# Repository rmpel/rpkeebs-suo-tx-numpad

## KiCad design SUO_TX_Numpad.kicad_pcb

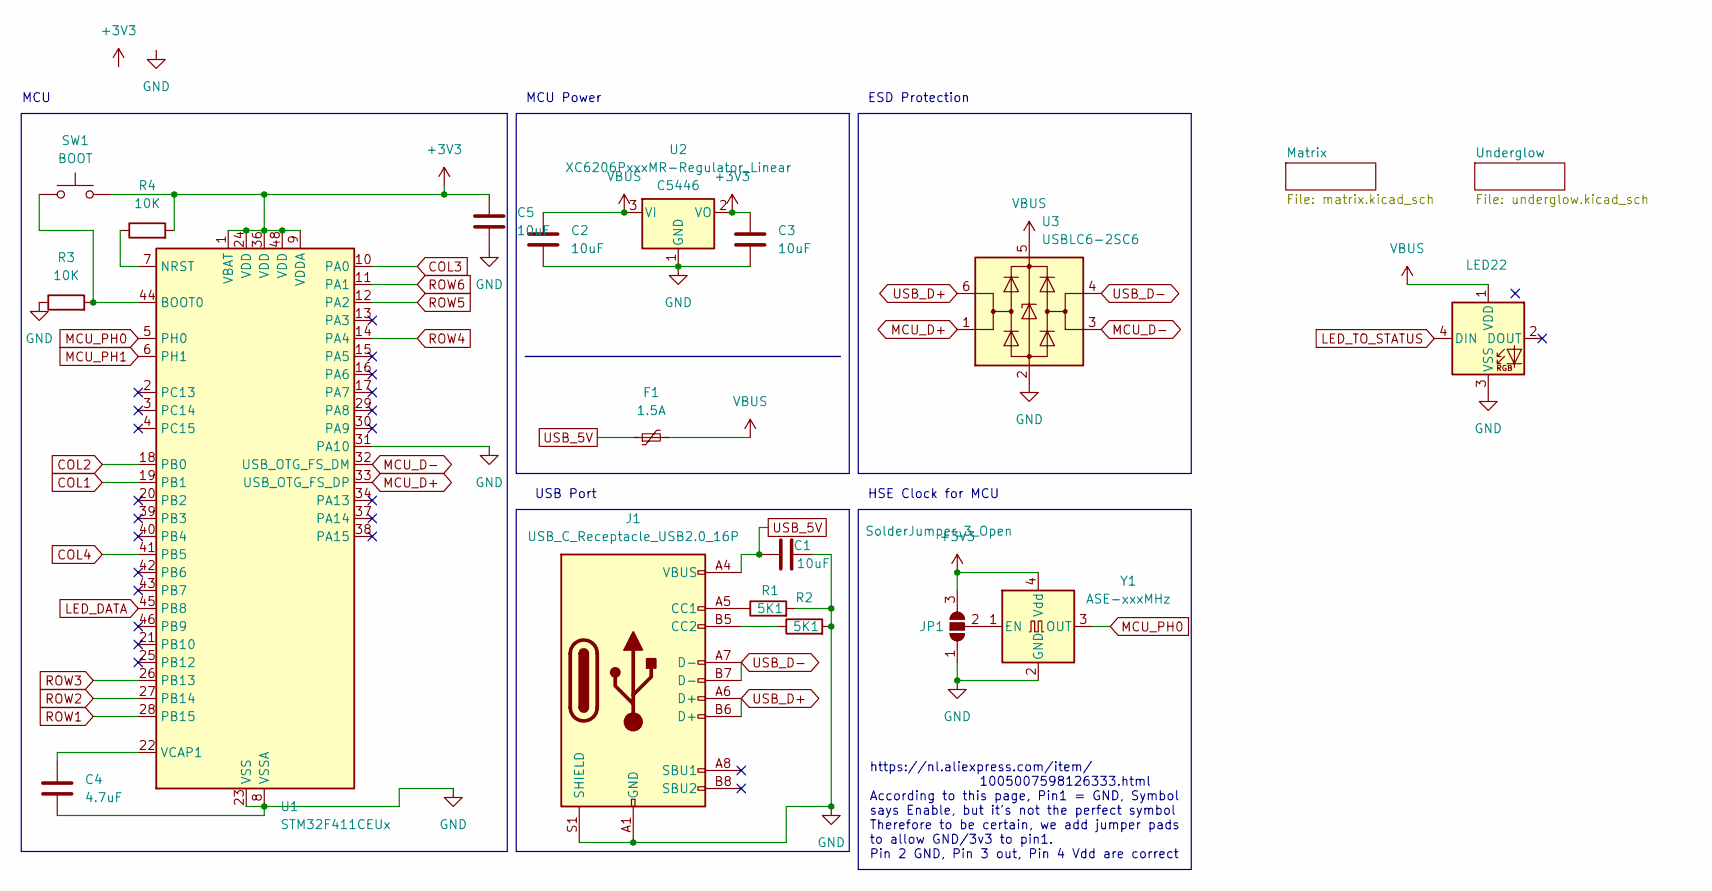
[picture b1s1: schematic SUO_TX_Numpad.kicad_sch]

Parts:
C1, C2, C3, C5: 10uF; C_0805_2012Metric_Pad1.18x1.45mm_HandSolder; LCSC C49010152
C4: 4.7uF; C_0805_2012Metric_Pad1.18x1.45mm_HandSolder; LCSC C277499
F1: 1.5A; Fuse_1206_3216Metric_Pad1.42x1.75mm_HandSolder; LCSC C28326719
J1: USB_C_Receptacle_USB2.0_16P; USB_C_HRO_TYPE-C-31-M-12; LCSC C2765186
JP1: SolderJumper_3_Open; SolderJumper-3_P1.3mm_Open_RoundedPad1.0x1.5mm
LED22: SK6803MINI-E-001 LCSC C5242955; MX_SK6812MINI-E_REV_ROTATED; LCSC C5242955
R1, R2: 5K1; R_0805_2012Metric_Pad1.20x1.40mm_HandSolder; LCSC C2930296
R3, R4: 10K; R_0805_2012Metric_Pad1.20x1.40mm_HandSolder; LCSC C2930231
SW1: BOOT; SW_Push_1P1T_NO_CK_KMR2; LCSC C221676
U1: STM32F411CEUx; QFN-48-1EP_7x7mm_P0.5mm_EP5.6x5.6mm_ThermalVias; LCSC C60420
U2: XC6206PxxxMR-Regulator_Linear; SOT-23_Handsoldering; LCSC C5446
U3: USBLC6-2SC6; SOT-23-6_Handsoldering; LCSC C7519
Y1: ASE-xxxMHz; Oscillator_SMD_Abracon_ASE-4Pin_3.2x2.5mm

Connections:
+3V3: C3.1, C5.1, JP1.3 (B), R4.2, SW1.2, U1.1 (VBAT), U1.9 (VDDA), U1.24 (VDD), U1.36 (VDD), U1.48 (VDD), U2.2 (VO), Y1.4 (Vdd)
COL1: U1.19 (PB1); also elsewhere on the board
COL2: U1.18 (PB0); also elsewhere on the board
COL3: U1.10 (PA0); also elsewhere on the board
COL4: U1.41 (PB5); also elsewhere on the board
GND: C1.2, C2.2, C3.2, C4.2, C5.2, J1.A1 (GND), J1.A12 (GND), J1.B1 (GND), J1.B12 (GND), J1.S1 (SHIELD), JP1.1 (A), LED22.3 (VSS), R1.2, R2.2, R3.1, U1.8 (VSSA), U1.23 (VSS), U1.31 (PA10), U1.35 (VSS), U1.47 (VSS), U1.49 (VSS), U2.1 (GND), U3.2 (GND), Y1.2 (GND); also elsewhere on the board
LED_DATA: U1.45 (PB8); also elsewhere on the board
LED_TO_STATUS: LED22.4 (DIN); also elsewhere on the board
MCU_D+: U1.33 (USB_OTG_FS_DP), U3.1 (I/O1)
MCU_D-: U1.32 (USB_OTG_FS_DM), U3.3 (I/O2)
MCU_PH0: U1.5 (PH0), Y1.3 (OUT)
MCU_PH1: U1.6 (PH1)
unnamed: J1.A5 (CC1), R1.1
unnamed: J1.B5 (CC2), R2.1
unnamed: JP1.2 (C), Y1.1 (EN)
unnamed: R3.2, SW1.1, U1.44 (BOOT0)
unnamed: R4.1, U1.7 (NRST)
unnamed: C4.1, U1.22 (VCAP1)
ROW1: U1.28 (PB15); also elsewhere on the board
ROW2: U1.27 (PB14); also elsewhere on the board
ROW3: U1.26 (PB13); also elsewhere on the board
ROW4: U1.14 (PA4); also elsewhere on the board
ROW5: U1.12 (PA2); also elsewhere on the board
ROW6: U1.11 (PA1); also elsewhere on the board
USB_5V: C1.1, F1.1, J1.A4 (VBUS), J1.A9 (VBUS), J1.B4 (VBUS), J1.B9 (VBUS)
USB_D+: J1.A6 (D+), J1.B6 (D+), U3.6 (I/O1)
USB_D-: J1.A7 (D-), J1.B7 (D-), U3.4 (I/O2)
VBUS: C2.1, F1.2, LED22.1 (VDD), U2.3 (VI), U3.5 (VBUS); also elsewhere on the board

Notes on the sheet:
HSE Clock for MCU
USB Port
https://nl.aliexpress.com/item/ 1005007598126333.html According to this page, Pin1 = GND, Symbol says Enable, but it's not the perfect symbol Therefore to be certain, we add jumper pads to allow GND/3v3 to pin1. Pin 2 GND, Pin 3 out, Pin 4 Vdd are correct
MCU
MCU Power
ESD Protection

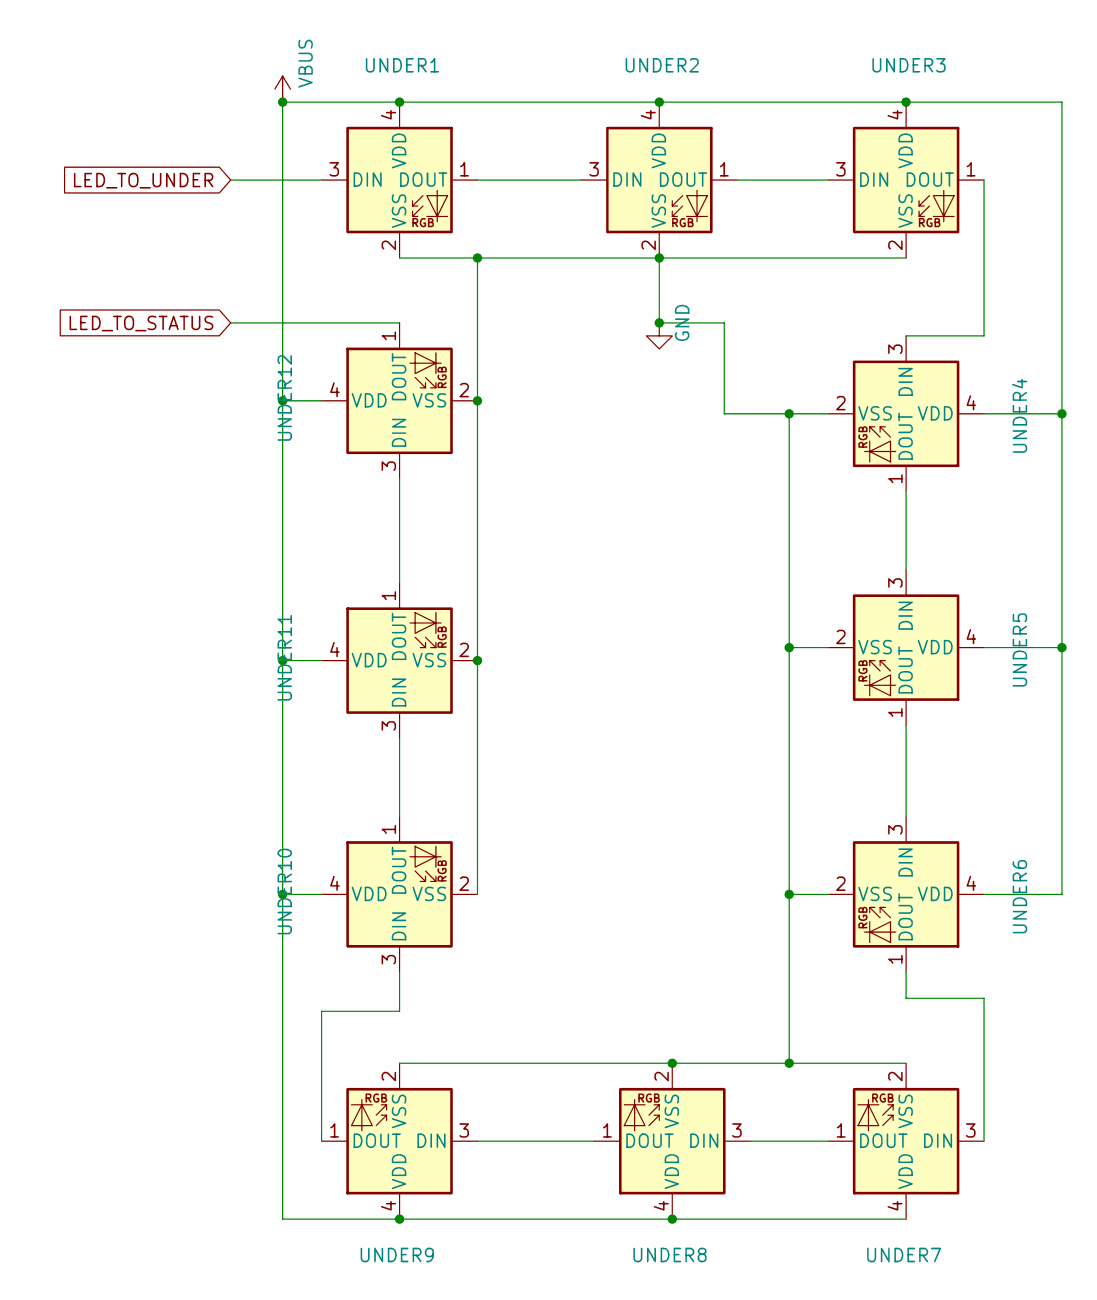
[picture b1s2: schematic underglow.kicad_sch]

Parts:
UNDER1, UNDER2, UNDER3, UNDER4, UNDER5, UNDER6, UNDER7, UNDER8, UNDER9, UNDER10, UNDER11, UNDER12: SK6812MINI LCSC C7423118; LED_SK6812MINI_PLCC4_3.5x3.5mm_P1.75mm; LCSC C7423118

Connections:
GND: UNDER1.2 (VSS), UNDER2.2 (VSS), UNDER3.2 (VSS), UNDER4.2 (VSS), UNDER5.2 (VSS), UNDER6.2 (VSS), UNDER7.2 (VSS), UNDER8.2 (VSS), UNDER9.2 (VSS), UNDER10.2 (VSS), UNDER11.2 (VSS), UNDER12.2 (VSS); also elsewhere on the board
LED_TO_STATUS: UNDER12.1 (DOUT); also elsewhere on the board
LED_TO_UNDER: UNDER1.3 (DIN); also elsewhere on the board
unnamed: UNDER1.1 (DOUT), UNDER2.3 (DIN)
unnamed: UNDER2.1 (DOUT), UNDER3.3 (DIN)
unnamed: UNDER3.1 (DOUT), UNDER4.3 (DIN)
unnamed: UNDER4.1 (DOUT), UNDER5.3 (DIN)
unnamed: UNDER5.1 (DOUT), UNDER6.3 (DIN)
unnamed: UNDER6.1 (DOUT), UNDER7.3 (DIN)
unnamed: UNDER7.1 (DOUT), UNDER8.3 (DIN)
unnamed: UNDER8.1 (DOUT), UNDER9.3 (DIN)
unnamed: UNDER9.1 (DOUT), UNDER10.3 (DIN)
unnamed: UNDER10.1 (DOUT), UNDER11.3 (DIN)
unnamed: UNDER11.1 (DOUT), UNDER12.3 (DIN)
VBUS: UNDER1.4 (VDD), UNDER2.4 (VDD), UNDER3.4 (VDD), UNDER4.4 (VDD), UNDER5.4 (VDD), UNDER6.4 (VDD), UNDER7.4 (VDD), UNDER8.4 (VDD), UNDER9.4 (VDD), UNDER10.4 (VDD), UNDER11.4 (VDD), UNDER12.4 (VDD); also elsewhere on the board

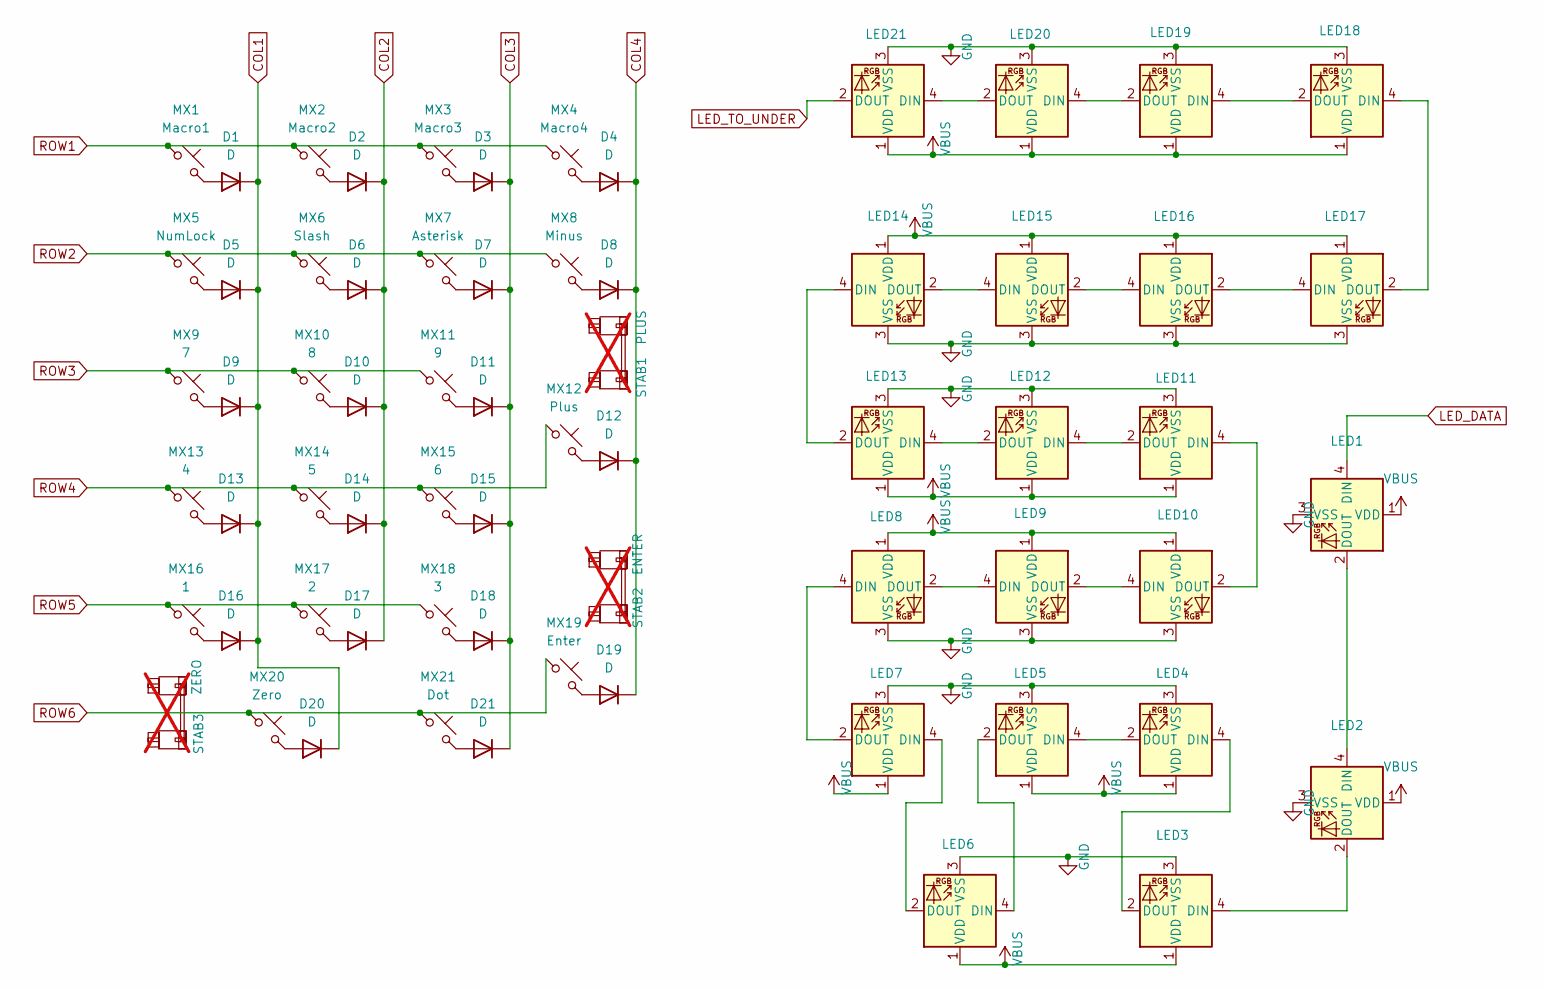
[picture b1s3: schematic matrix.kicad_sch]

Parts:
D1, D2, D3, D4, D5, D6, D7, D8, D9, D10, D11, D12, D13, D14, D15, D16, D17, D18, D19, D20, D21: D; Diode_SOD-123; LCSC C28646371
LED1, LED2, LED3, LED4, LED5, LED6, LED7, LED8, LED9, LED10, LED11, LED12, LED13, LED14, LED15, LED16, LED17, LED18, LED19, LED20, LED21: SK6803MINI-E-001 LCSC C5242955; MX_SK6812MINI-E_REV_ROTATED; LCSC C5242955
MX1: Macro1; Hotswap_MX_Plated_1.00u; LCSC C5156480
MX2: Macro2; Hotswap_MX_Plated_1.00u; LCSC C5156480
MX3: Macro3; Hotswap_MX_Plated_1.00u; LCSC C5156480
MX4: Macro4; Hotswap_MX_Plated_1.00u; LCSC C5156480
MX5: NumLock; Hotswap_MX_Plated_1.00u; LCSC C5156480
MX6: Slash; Hotswap_MX_Plated_1.00u; LCSC C5156480
MX7: Asterisk; Hotswap_MX_Plated_1.00u; LCSC C5156480
MX8: Minus; Hotswap_MX_Plated_1.00u; LCSC C5156480
MX9: 7; Hotswap_MX_Plated_1.00u; LCSC C5156480
MX10: 8; Hotswap_MX_Plated_1.00u; LCSC C5156480
MX11: 9; Hotswap_MX_Plated_1.00u; LCSC C5156480
MX12: Plus; Hotswap_MX_Plated_2.00u; LCSC C5156480
MX13: 4; Hotswap_MX_Plated_1.00u; LCSC C5156480
MX14: 5; Hotswap_MX_Plated_1.00u; LCSC C5156480
MX15: 6; Hotswap_MX_Plated_1.00u; LCSC C5156480
MX16: 1; Hotswap_MX_Plated_1.00u; LCSC C5156480
MX17: 2; Hotswap_MX_Plated_1.00u; LCSC C5156480
MX18: 3; Hotswap_MX_Plated_1.00u; LCSC C5156480
MX19: Enter; Hotswap_MX_Plated_2.00u; LCSC C5156480
MX20: Zero; Hotswap_MX_Plated_2.00u; LCSC C5156480
MX21: Dot; Hotswap_MX_Plated_1.00u; LCSC C5156480
STAB1: PLUS; Stabilizer_MX_2.00u; not fitted
STAB2: ENTER; Stabilizer_MX_2.00u; not fitted
STAB3: ZERO; Stabilizer_MX_2.00u; not fitted

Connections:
COL1: D1.1 (K), D5.1 (K), D9.1 (K), D13.1 (K), D16.1 (K), D20.1 (K); also elsewhere on the board
COL2: D2.1 (K), D6.1 (K), D10.1 (K), D14.1 (K), D17.1 (K); also elsewhere on the board
COL3: D3.1 (K), D7.1 (K), D11.1 (K), D15.1 (K), D18.1 (K), D21.1 (K); also elsewhere on the board
COL4: D4.1 (K), D8.1 (K), D12.1 (K), D19.1 (K); also elsewhere on the board
GND: LED1.3 (VSS), LED2.3 (VSS), LED3.3 (VSS), LED4.3 (VSS), LED5.3 (VSS), LED6.3 (VSS), LED7.3 (VSS), LED8.3 (VSS), LED9.3 (VSS), LED10.3 (VSS), LED11.3 (VSS), LED12.3 (VSS), LED13.3 (VSS), LED14.3 (VSS), LED15.3 (VSS), LED16.3 (VSS), LED17.3 (VSS), LED18.3 (VSS), LED19.3 (VSS), LED20.3 (VSS), LED21.3 (VSS); also elsewhere on the board
LED_DATA: LED1.4 (DIN); also elsewhere on the board
LED_TO_UNDER: LED21.2 (DOUT); also elsewhere on the board
unnamed: D1.2 (A), MX1.2
unnamed: D2.2 (A), MX2.2
unnamed: D3.2 (A), MX3.2
unnamed: D4.2 (A), MX4.2
unnamed: D5.2 (A), MX5.2
unnamed: D6.2 (A), MX6.2
unnamed: D7.2 (A), MX7.2
unnamed: D8.2 (A), MX8.2
unnamed: D9.2 (A), MX9.2
unnamed: D10.2 (A), MX10.2
unnamed: D11.2 (A), MX11.2
unnamed: D12.2 (A), MX12.2
unnamed: D13.2 (A), MX13.2
unnamed: D14.2 (A), MX14.2
unnamed: D15.2 (A), MX15.2
unnamed: D16.2 (A), MX16.2
unnamed: D17.2 (A), MX17.2
unnamed: D18.2 (A), MX18.2
unnamed: D19.2 (A), MX19.2
unnamed: D20.2 (A), MX20.2
unnamed: D21.2 (A), MX21.2
unnamed: LED1.2 (DOUT), LED2.4 (DIN)
unnamed: LED2.2 (DOUT), LED3.4 (DIN)
unnamed: LED3.2 (DOUT), LED4.4 (DIN)
unnamed: LED4.2 (DOUT), LED5.4 (DIN)
unnamed: LED5.2 (DOUT), LED6.4 (DIN)
unnamed: LED6.2 (DOUT), LED7.4 (DIN)
unnamed: LED7.2 (DOUT), LED8.4 (DIN)
unnamed: LED8.2 (DOUT), LED9.4 (DIN)
unnamed: LED9.2 (DOUT), LED10.4 (DIN)
unnamed: LED10.2 (DOUT), LED11.4 (DIN)
unnamed: LED11.2 (DOUT), LED12.4 (DIN)
unnamed: LED12.2 (DOUT), LED13.4 (DIN)
unnamed: LED13.2 (DOUT), LED14.4 (DIN)
unnamed: LED14.2 (DOUT), LED15.4 (DIN)
unnamed: LED15.2 (DOUT), LED16.4 (DIN)
unnamed: LED16.2 (DOUT), LED17.4 (DIN)
unnamed: LED17.2 (DOUT), LED18.4 (DIN)
unnamed: LED18.2 (DOUT), LED19.4 (DIN)
unnamed: LED19.2 (DOUT), LED20.4 (DIN)
unnamed: LED20.2 (DOUT), LED21.4 (DIN)
ROW1: MX1.1, MX2.1, MX3.1, MX4.1; also elsewhere on the board
ROW2: MX5.1, MX6.1, MX7.1, MX8.1; also elsewhere on the board
ROW3: MX9.1, MX10.1, MX11.1; also elsewhere on the board
ROW4: MX12.1, MX13.1, MX14.1, MX15.1; also elsewhere on the board
ROW5: MX16.1, MX17.1, MX18.1; also elsewhere on the board
ROW6: MX19.1, MX20.1, MX21.1; also elsewhere on the board
VBUS: LED1.1 (VDD), LED2.1 (VDD), LED3.1 (VDD), LED4.1 (VDD), LED5.1 (VDD), LED6.1 (VDD), LED7.1 (VDD), LED8.1 (VDD), LED9.1 (VDD), LED10.1 (VDD), LED11.1 (VDD), LED12.1 (VDD), LED13.1 (VDD), LED14.1 (VDD), LED15.1 (VDD), LED16.1 (VDD), LED17.1 (VDD), LED18.1 (VDD), LED19.1 (VDD), LED20.1 (VDD), LED21.1 (VDD); also elsewhere on the board

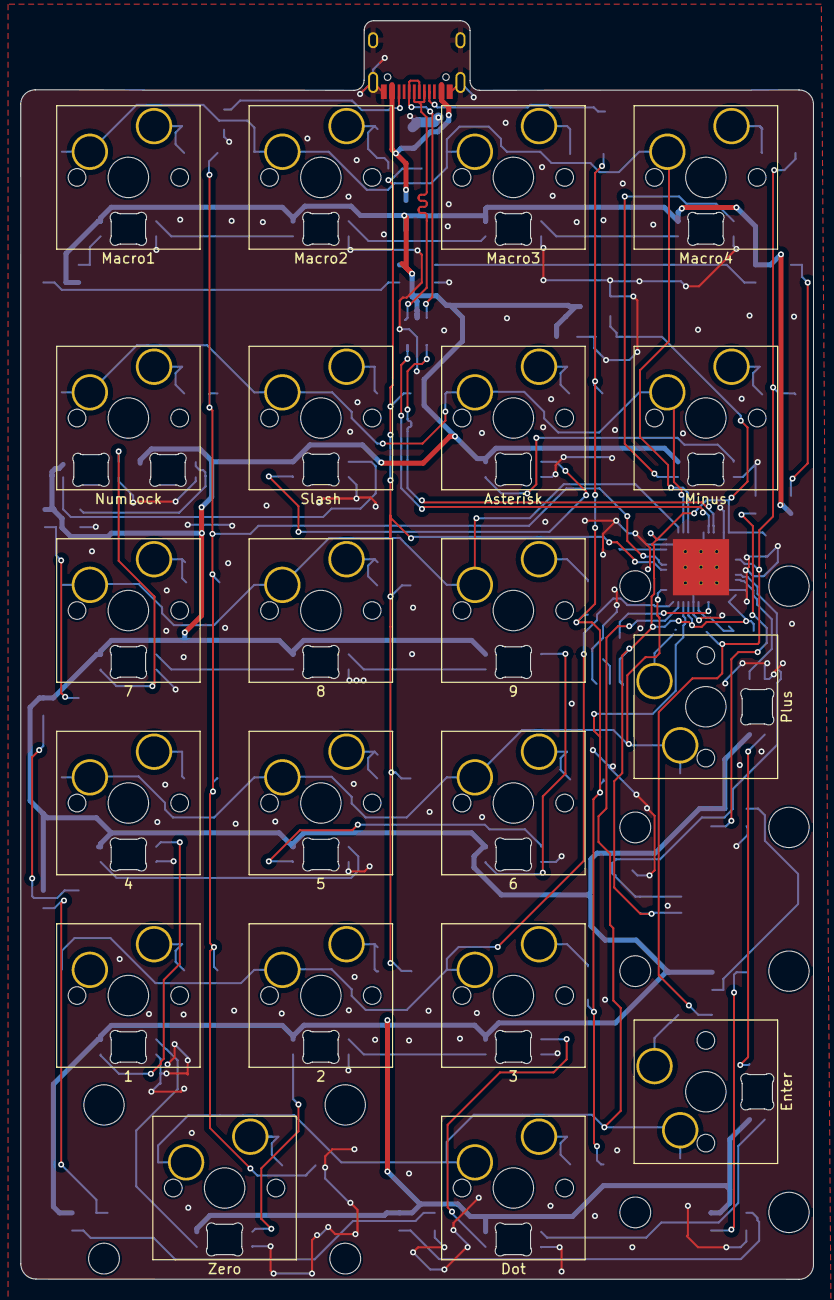
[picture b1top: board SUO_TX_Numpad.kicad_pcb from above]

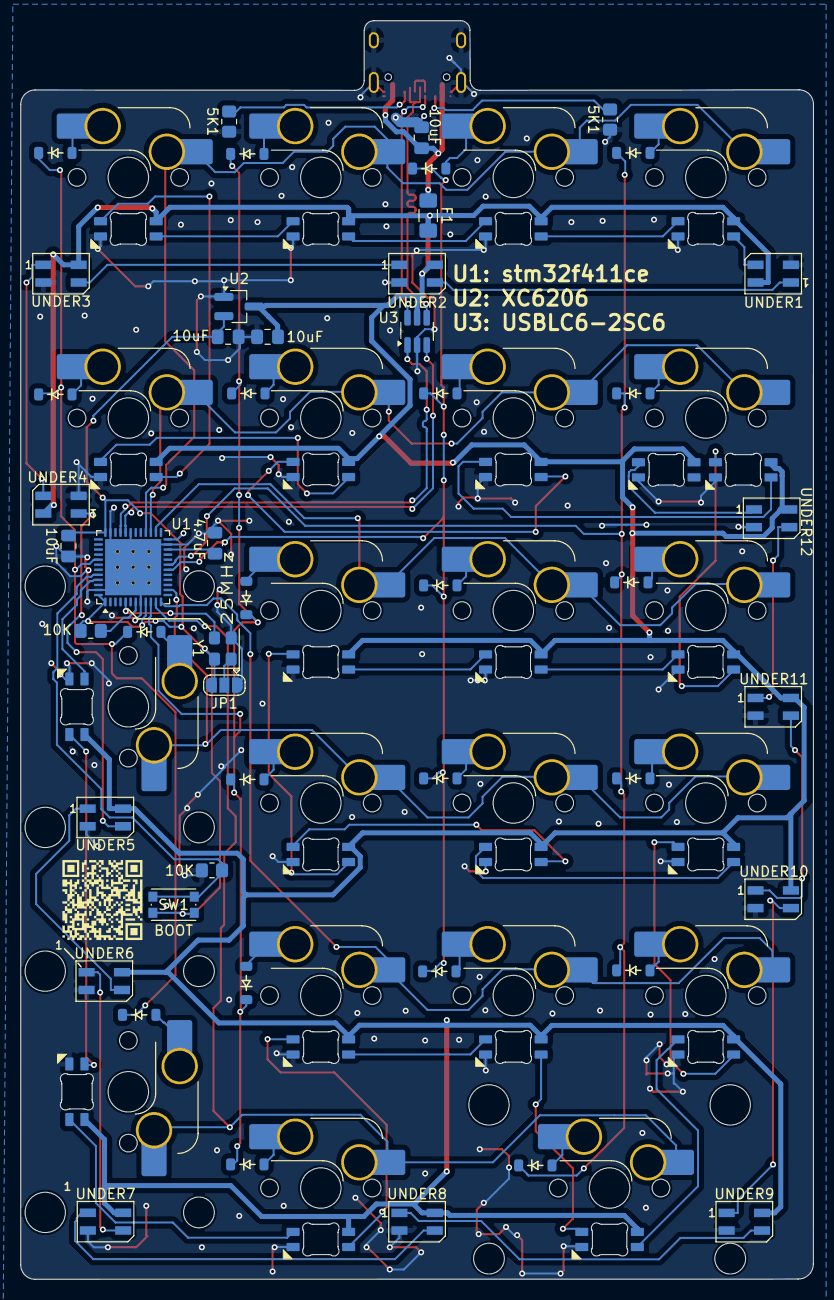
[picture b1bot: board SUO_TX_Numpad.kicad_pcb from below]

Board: 2 copper layers, 78.5 x 124.6 mm, 96 parts (49 on the bottom side), 80 nets.

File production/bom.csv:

Designator,Footprint,Quantity,Value,LCSC Part #,DigiKey,info
"C1, C2, C3, C5",0805,4,10uF,C49010152,CL21A106KOQNNNE,
"D1, D10, D11, D12, D13, D14, D15, D16, D17, D18, D19, D2, D20, D21, D3, D4, D5, D6, D7, D8, D9",Diode_SOD-123,21,D,C28646371,1N4148W-TP,
F1,1206,1,1.5A,C28326719,1206L075THYR,
J1,USB_C_HRO_TYPE-C-31-M-12,1,USB_C_Receptacle_USB2.0_16P,C2765186,UJ20-C-H-G-SMT-1-P16-TR,
"LED1, LED10, LED11, LED12, LED13, LED14, LED15, LED16, LED17, LED18, LED19, LED2, LED20, LED21, LED22, LED3, LED4, LED5, LED6, LED7, LED8, LED9",MX_SK6812MINI-E_REV,22,SK6803MINI-E-001 LCSC C5242955,C5242955,,
MX1-MX21,Hotswap_MX_Plated_1.00u,21,Macro1,C5156480,,,
"R1, R2, R3, R4, R5, R6",0805,6,5K1,C2930296,RC0805FR-075K1L,
SW1,SW_Push_1P1T_NO_CK_KMR2,1,BOOT,C221676,PTS636SK25FSMTR LFS,
U1,QFN-48-1EP_7x7mm_P0.5mm_EP5.6x5.6mm_ThermalVias,1,STM32F411CEUx,C60420,497-14907-ND,
U2,SOT-23_Handsoldering,1,XC6206PxxxMR-Regulator_Linear,C5446,XC6206P332MR-G,
U3,SOT-23-6_Handsoldering,1,USBLC6-2SC6,C7519,USBLC6-2SC6,,
"UNDER1, UNDER10, UNDER11, UNDER12, UNDER2, UNDER3, UNDER4, UNDER5, UNDER6, UNDER7, UNDER8, UNDER9",LED_SK6812MINI_PLCC4_3.5x3.5mm_P1.75mm,12,SK6812MINI LCSC C7423118,C7423118,S35353RGBSK6812MINID001,
C4,0805,1,4.7uF,C277499,,
Y1,Oscillator_SMD 3225 Active,1,XTAL OSC XO 25.0000MHZ HCMOS SMD,,,https://nl.aliexpress.com/item/1005007598126333.html

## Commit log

2026-03-22 ongoing
2026-03-22 Routing done, violations handled, Silk screen cleaned up
2026-03-22 Add QR to silk
2026-03-23 Added LCSC, but going to switch to 0603 or 0804 components as I want to keep handsoldering an option
2026-03-23 Switched to 0805 for R C and SOD-123 for Diodes
2026-03-23 Add production files - make note - the BOM seems totally incorrect
2026-03-24 Updated BOM
2026-03-26 Wrong diode package/type in bom C917030 is 1N4148w SOD-123 switching diode
2026-03-29 PCB Layout altered to be exact to a SUO TX TKL board, Y-dimensions-wise
2026-03-30 Made board slightly smaller, un-rotated the plus and enter stabilisers, they are supposed to go inward and not outward
2026-03-31 manually updated BOM for DigiKey support
2026-03-31 Added fixed copy of bom for future reference
2026-04-03 Fixed VCAP1 Value to 4.7 uF, added XTAL 8 MHz
2026-04-06 Pulled A10 to ground; found that a BlackPill dev board wo'nt DFU properly without it. Updated SK6812MINI-E footprint to be a rotated one; track layout stays the same, but the old footprint was incorr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
2026-04-06 Added freqency marker for HCMOS XTAL
2026-04-06 Updated production files.
2026-04-09 Added 3225 active oscillator, unsure if pin 1 is in fact enable, is in fact active high, so a jumper pad to pick either is added
2026-04-12 Fixed wiring mistake on USBLC6-2SC6
